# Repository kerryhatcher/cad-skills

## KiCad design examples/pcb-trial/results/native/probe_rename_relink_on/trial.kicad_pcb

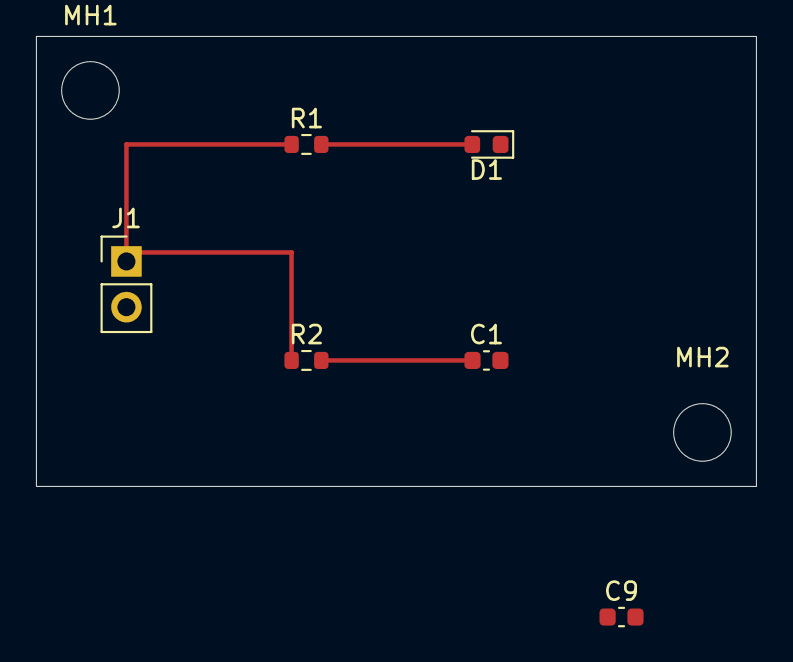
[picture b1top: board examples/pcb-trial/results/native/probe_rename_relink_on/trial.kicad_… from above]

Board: 2 copper layers, 40.0 x 25.0 mm, 8 parts (0 on the bottom side), 4 nets.

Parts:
C1, C9: 100n; C_0603_1608Metric
D1: Green; LED_0603_1608Metric
J1: Power; PinHeader_1x02_P2.54mm_Vertical
MH1, MH2: M3; MountingHole_3.2mm_M3
R1: 1k; R_0603_1608Metric
R2: 10k; R_0603_1608Metric

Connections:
/GND: C1.2, C9.2, D1.1 (K), J1.2
/N_LED: D1.2 (A), R1.2
/N_RC: C1.1, C9.1, R2.2
/VIN: J1.1, R1.1, R2.1

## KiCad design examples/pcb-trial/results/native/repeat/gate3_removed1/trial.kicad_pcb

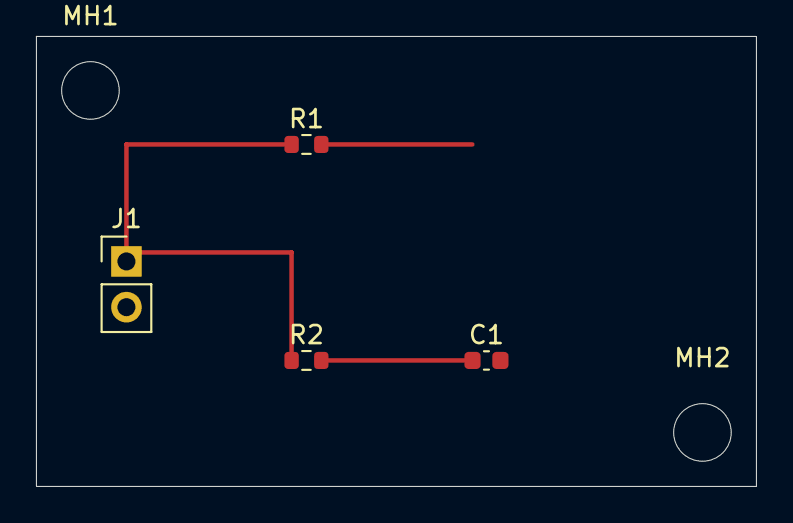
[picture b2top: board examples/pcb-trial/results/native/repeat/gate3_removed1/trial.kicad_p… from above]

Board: 2 copper layers, 40.0 x 25.0 mm, 6 parts (0 on the bottom side), 3 nets.

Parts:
C1: 100n; C_0603_1608Metric
J1: Power; PinHeader_1x02_P2.54mm_Vertical
MH1, MH2: M3; MountingHole_3.2mm_M3
R1: 1k; R_0603_1608Metric
R2: 10k; R_0603_1608Metric

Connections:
/GND: C1.2, J1.2
/N_RC: C1.1, R2.2
/VIN: J1.1, R1.1, R2.1
